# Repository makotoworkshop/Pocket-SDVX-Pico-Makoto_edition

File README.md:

# SDVX Pico Makoto's Édition − based on SpeedyPotato's Pocket-SDVX-Pico-v4 −
Pocket SDVX Pico Makoto's Édition source files, production files, and documentation

This work is licensed under a Creative Commons Attribution-NonCommercial-ShareAlike 4.0 International License.

- All documentation « how to » is here : https://burogu.makotoworkshop.org/index.php?pages/Menu_pocket_sdvx
- Firmware is here : https://github.com/makotoworkshop/Pico-Game-Controller-v4_Makoto-edition

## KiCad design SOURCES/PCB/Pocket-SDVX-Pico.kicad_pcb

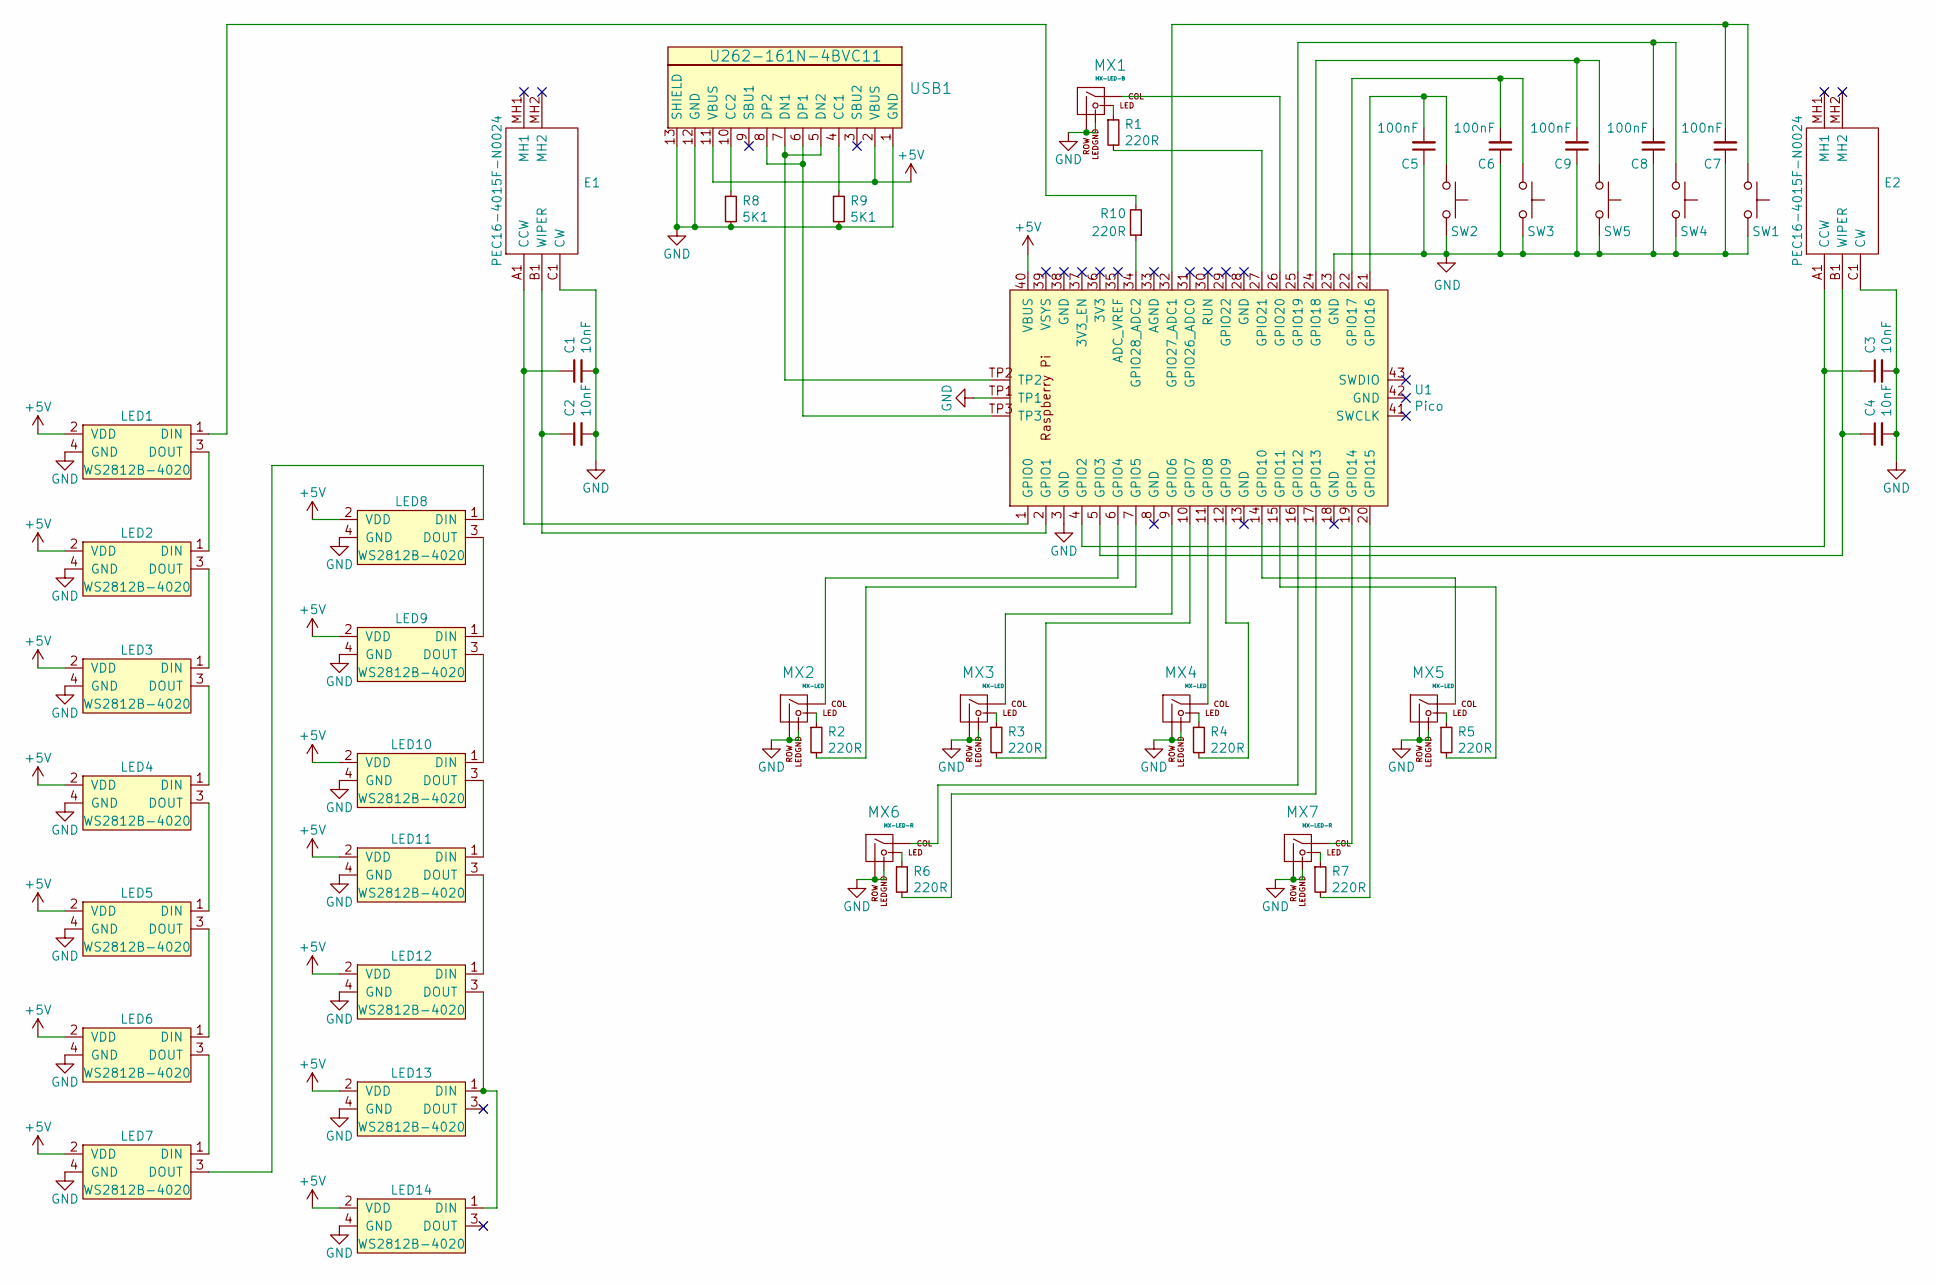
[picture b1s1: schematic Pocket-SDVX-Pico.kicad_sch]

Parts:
C1, C2, C3, C4: 10nF; C_1206_3216Metric_Pad1.33x1.80mm_HandSolder; LCSC C57112
C5, C6, C7, C8, C9: 100nF; C_1206_3216Metric_Pad1.33x1.80mm_HandSolder; LCSC C57112
E1, E2: PEC16-4015F-N0024; PEC16-4015F-N0024-millmax; Mouser Part Number 652-PEC16-4015FN0024
LED1, LED2, LED3, LED4, LED5, LED6, LED7, LED8, LED9, LED10, LED11, LED12, LED13, LED14: WS2812B-4020
MX1: MX-LED-B; MXOnly-1.5U-Hotswap-LED-SMD; LCSC C440444
MX2, MX3, MX4, MX5: MX-LED; MXOnly-1.5U-Hotswap-LED-SMD; LCSC C26545
MX6, MX7: MX-LED-R; MXOnly-1.5U-Hotswap-LED-SMD; LCSC C440441
R1, R2, R3, R4, R5, R6, R7, R10: 220R; R_1206_3216Metric_Pad1.30x1.75mm_HandSolder; LCSC C22962
R8, R9: 5K1; R_1206_3216Metric_Pad1.30x1.75mm_HandSolder; LCSC C23186
SW1, SW2, SW3, SW4, SW5: SW_Push; SW_Tactile_SPST_Angled_PTS645Vx83-2LFS
U1: Pico; RPi_Pico_SMD_TH
USB1: U262-161N-4BVC11; HRO-TYPE-C-31-M-12-Assembly; LCSC C319148

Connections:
+5V: LED1.2 (VDD), LED2.2 (VDD), LED3.2 (VDD), LED4.2 (VDD), LED5.2 (VDD), LED6.2 (VDD), LED7.2 (VDD), LED8.2 (VDD), LED9.2 (VDD), LED10.2 (VDD), LED11.2 (VDD), LED12.2 (VDD), LED13.2 (VDD), LED14.2 (VDD), U1.40 (VBUS), USB1.2 (VBUS), USB1.11 (VBUS)
GND: C1.2, C2.2, C3.2, C4.2, C5.1, C6.1, C7.1, C8.1, C9.1, E1.C1 (CW), E2.C1 (CW), LED1.4 (GND), LED2.4 (GND), LED3.4 (GND), LED4.4 (GND), LED5.4 (GND), LED6.4 (GND), LED7.4 (GND), LED8.4 (GND), LED9.4 (GND), LED10.4 (GND), LED11.4 (GND), LED12.4 (GND), LED13.4 (GND), LED14.4 (GND), MX1.2 (ROW), MX1.4 (LEDGND), MX2.2 (ROW), MX2.4 (LEDGND), MX3.2 (ROW), MX3.4 (LEDGND), MX4.2 (ROW), MX4.4 (LEDGND), MX5.2 (ROW), MX5.4 (LEDGND), MX6.2 (ROW), MX6.4 (LEDGND), MX7.2 (ROW), MX7.4 (LEDGND), R8.2, R9.2, SW1.2, SW2.2, SW3.2, SW4.2, SW5.2, U1.3 (GND), U1.23 (GND), U1.TP1, USB1.1 (GND), USB1.12 (GND), USB1.13 (SHIELD)
unnamed: C1.1, E1.A1 (CCW), U1.1 (GPIO0)
unnamed: C2.1, E1.B1 (WIPER), U1.2 (GPIO1)
unnamed: C3.1, E2.A1 (CCW), U1.4 (GPIO2)
unnamed: C4.1, E2.B1 (WIPER), U1.5 (GPIO3)
unnamed: LED1.1 (DIN), R10.2
unnamed: LED1.3 (DOUT), LED2.1 (DIN)
unnamed: LED2.3 (DOUT), LED3.1 (DIN)
unnamed: LED3.3 (DOUT), LED4.1 (DIN)
unnamed: LED4.3 (DOUT), LED5.1 (DIN)
unnamed: LED5.3 (DOUT), LED6.1 (DIN)
unnamed: LED6.3 (DOUT), LED7.1 (DIN)
unnamed: LED7.3 (DOUT), LED8.1 (DIN)
unnamed: LED8.3 (DOUT), LED9.1 (DIN)
unnamed: LED9.3 (DOUT), LED10.1 (DIN)
unnamed: LED10.3 (DOUT), LED11.1 (DIN)
unnamed: LED11.3 (DOUT), LED12.1 (DIN)
unnamed: LED12.3 (DOUT), LED13.1 (DIN), LED14.1 (DIN)
unnamed: MX1.1 (COL), U1.26 (GPIO20)
unnamed: MX1.3 (LED), R1.1
unnamed: MX2.1 (COL), U1.6 (GPIO4)
unnamed: MX2.3 (LED), R2.1
unnamed: MX3.1 (COL), U1.9 (GPIO6)
unnamed: MX3.3 (LED), R3.1
unnamed: MX4.1 (COL), U1.11 (GPIO8)
unnamed: MX4.3 (LED), R4.1
unnamed: MX5.1 (COL), U1.14 (GPIO10)
unnamed: MX5.3 (LED), R5.1
unnamed: MX6.1 (COL), U1.16 (GPIO12)
unnamed: MX6.3 (LED), R6.1
unnamed: MX7.1 (COL), U1.19 (GPIO14)
unnamed: MX7.3 (LED), R7.1
unnamed: R2.2, U1.7 (GPIO5)
unnamed: R3.2, U1.10 (GPIO7)
unnamed: R4.2, U1.12 (GPIO9)
unnamed: R5.2, U1.15 (GPIO11)
unnamed: R6.2, U1.17 (GPIO13)
unnamed: R7.2, U1.20 (GPIO15)
unnamed: C5.2, SW2.1, U1.21 (GPIO16)
unnamed: C6.2, SW3.1, U1.22 (GPIO17)
unnamed: C9.2, SW5.1, U1.24 (GPIO18)
unnamed: C8.2, SW4.1, U1.25 (GPIO19)
unnamed: R1.2, U1.27 (GPIO21)
unnamed: C7.2, SW1.1, U1.32 (GPIO27_ADC1)
unnamed: R10.1, U1.34 (GPIO28_ADC2)
unnamed: R9.1, USB1.4 (CC1)
unnamed: R8.1, USB1.10 (CC2)
unnamed: U1.TP2, USB1.5 (DN2), USB1.7 (DN1)
unnamed: U1.TP3, USB1.6 (DP1), USB1.8 (DP2)

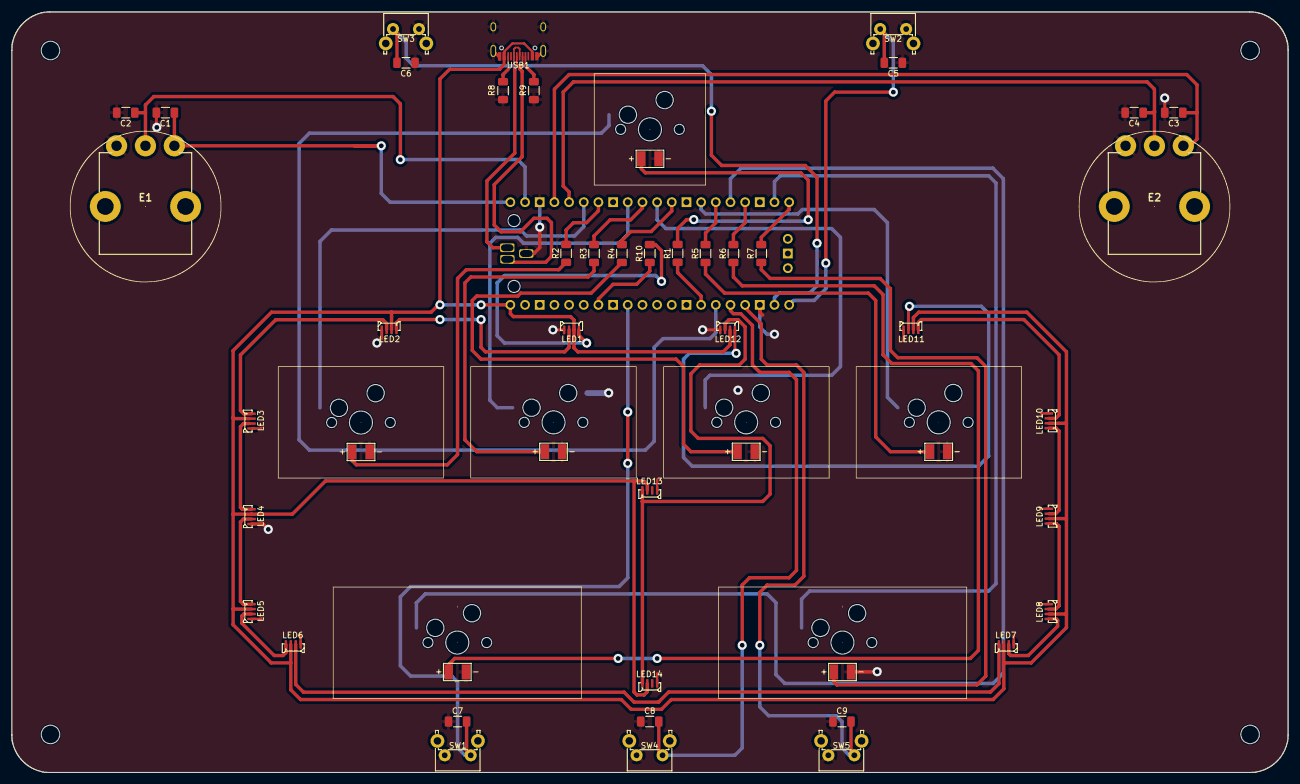
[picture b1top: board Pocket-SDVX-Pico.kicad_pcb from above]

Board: 2 copper layers, 220.9 x 131.7 mm, 49 parts (1 on the bottom side), 50 nets.
